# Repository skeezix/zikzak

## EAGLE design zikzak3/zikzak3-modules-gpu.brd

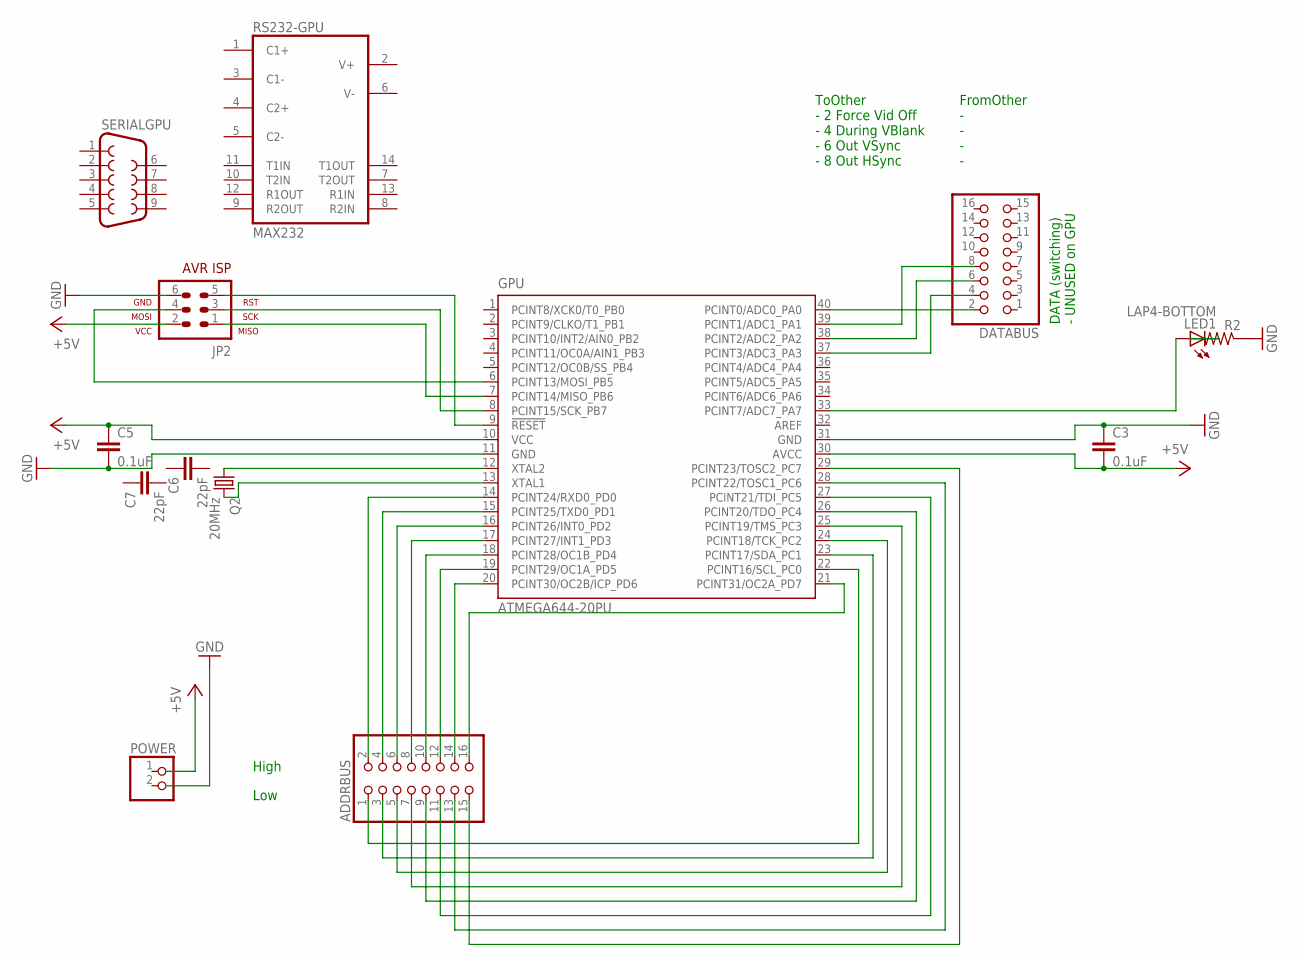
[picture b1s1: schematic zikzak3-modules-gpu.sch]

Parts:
ADDRBUS: PINHD-2X8/90; 2X08/90
C3, C5: 0.1uF; C2.5-3
C6, C7: 22pF; C2.5-3
DATABUS: PINHD-2X8/90; 2X08/90
GPU: ATMEGA644-20PU; DIL40
JP2: AVR-ISP-6VERT; AVR-ISP-6
LED1: LAP4-BOTTOM; P47F-BOTTOM
POWER: PINHD-1X2; 1X02
Q2: 20MHz; TC38H
R2: R-US_0204/2V; 0204V
RS232-GPU: MAX232; DIL16
SERIALGPU: F09H

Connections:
+5V: C3.2, C5.1, GPU.10 (VCC), GPU.30 (AVCC), JP2.2
GND: C3.1, C5.2, GPU.11 (GND), GPU.31 (GND), JP2.6, R2.1, RS232-GPU.15 (GND)
unnamed: ADDRBUS.16, GPU.21 (PCINT31/OC2A_PD7)
unnamed: ADDRBUS.14, GPU.20 (PCINT30/OC2B/ICP_PD6)
unnamed: ADDRBUS.12, GPU.19 (PCINT29/OC1A_PD5)
unnamed: ADDRBUS.2, GPU.14 (PCINT24/RXD0_PD0)
unnamed: ADDRBUS.4, GPU.15 (PCINT25/TXD0_PD1)
unnamed: ADDRBUS.6, GPU.16 (PCINT26/INT0_PD2)
unnamed: ADDRBUS.8, GPU.17 (PCINT27/INT1_PD3)
unnamed: ADDRBUS.10, GPU.18 (PCINT28/OC1B_PD4)
unnamed: GPU.12 (XTAL2), Q2.1
unnamed: GPU.13 (XTAL1), Q2.2
unnamed: ADDRBUS.1, GPU.22 (PCINT16/SCL_PC0)
unnamed: ADDRBUS.3, GPU.23 (PCINT17/SDA_PC1)
unnamed: ADDRBUS.5, GPU.24 (PCINT18/TCK_PC2)
unnamed: ADDRBUS.7, GPU.25 (PCINT19/TMS_PC3)
unnamed: ADDRBUS.9, GPU.26 (PCINT20/TDO_PC4)
unnamed: ADDRBUS.11, GPU.27 (PCINT21/TDI_PC5)
unnamed: ADDRBUS.13, GPU.28 (PCINT22/TOSC1_PC6)
unnamed: ADDRBUS.15, GPU.29 (PCINT23/TOSC2_PC7)
unnamed: LED1.C, R2.2
unnamed: GPU.33 (PCINT7/ADC7_PA7), LED1.A
unnamed: DATABUS.2, GPU.40 (PCINT0/ADC0_PA0)
unnamed: DATABUS.4, GPU.37 (PCINT3/ADC3_PA3)
unnamed: DATABUS.6, GPU.38 (PCINT2/ADC2_PA2)
unnamed: DATABUS.8, GPU.39 (PCINT1/ADC1_PA1)
unnamed: GPU.6 (PCINT13/MOSI_PB5), JP2.4
unnamed: GPU.7 (PCINT14/MISO_PB6), JP2.1
unnamed: GPU.8 (PCINT15/SCK_PB7), JP2.3
unnamed: GPU.9 (!RESET), JP2.5
VCC: RS232-GPU.16 (VCC)

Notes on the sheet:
DATA (switching) - UNUSED on GPU
ToOther - 2 Force Vid Off - 4 During VBlank - 6 Out VSync - 8 Out HSync
Low
High
FromOther - - - -

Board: 2 copper layers, 14 parts (1 on the bottom side), 30 nets, no tracks yet.
